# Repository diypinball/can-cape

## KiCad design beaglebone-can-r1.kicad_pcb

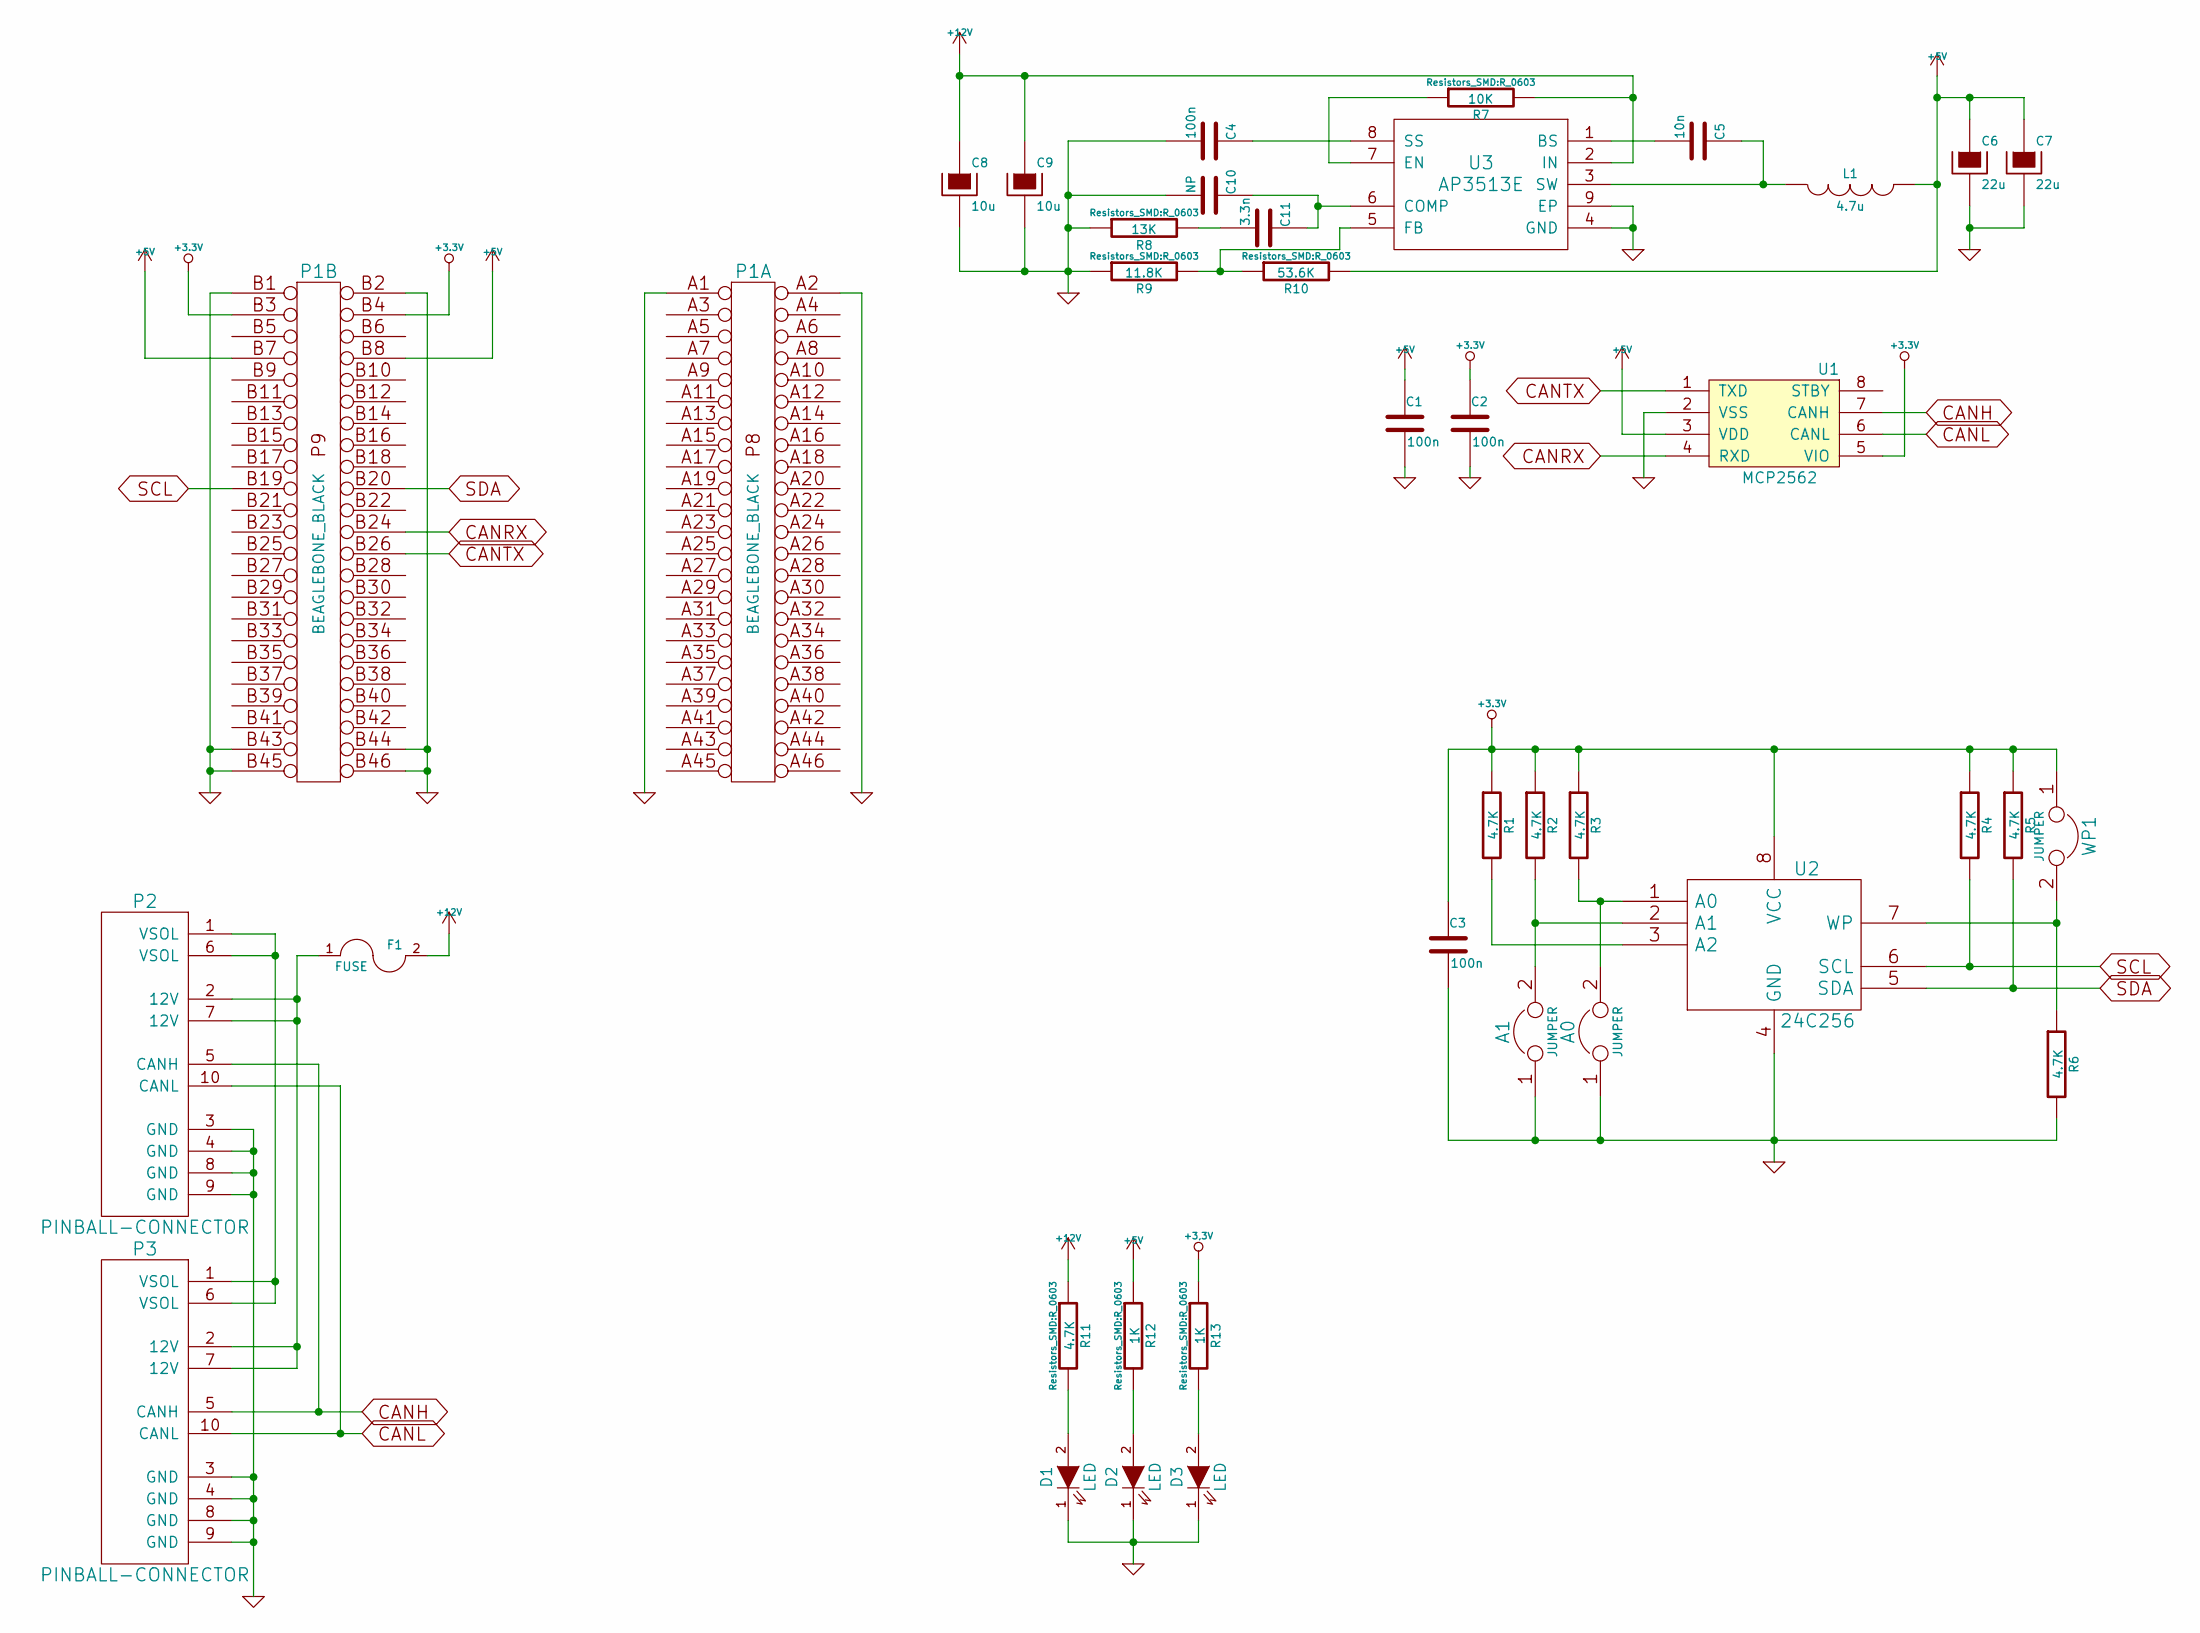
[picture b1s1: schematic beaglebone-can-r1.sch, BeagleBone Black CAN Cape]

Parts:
A0, A1: JUMPER; S_JUMPER_2
C1, C2, C3, C4: 100n; C_0603
C5: 10n; C_0603
C6, C7: 22u; c_elec_5x5.8
C8, C9: 10u; c_elec_5x5.8
C10: NP; C_0603
C11: 3.3n; C_0603
D1, D2, D3: LED; LED-0603
F1: FUSE; FC203-20MM
L1: 4.7u; SELF-WE-PD-XXL
P1: BEAGLEBONE_BLACK
P2, P3: PINBALL-CONNECTOR; PINBALL-CONNECTOR-V
R1, R2, R3, R4, R5, R6, R11: 4.7K; R_0603
R7: 10K; R_0603
R8: 13K; R_0603
R9: 11.8K; R_0603
R10: 53.6K; R_0603
R12, R13: 1K; R_0603
U1: MCP2562; SOIC-8_3.9x4.9mm_Pitch1.27mm
U2: 24C256; SOIC-8_3.9x4.9mm_Pitch1.27mm
U3: AP3513E; SOIC-8-1EP_3.9x4.9mm_Pitch1.27mm
WP1: JUMPER; S_JUMPER_2

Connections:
+5V: C1.1, C6.1, C7.1, L1.2, P1.B7 (P7), P1.B8 (P8), R10.2, R12.1, U1.3 (VDD)
+12V: C8.1, C9.1, F1.2, R7.2, R11.1, U3.2 (IN)
CANH: P2.5 (CANH), P3.5 (CANH), U1.7 (CANH)
CANL: P2.10 (CANL), P3.10 (CANL), U1.6 (CANL)
CANRX: P1.B24 (P24), U1.4 (RXD)
CANTX: P1.B26 (P26), U1.1 (TXD)
GND: A0.1, A1.1, C1.2, C2.2, C3.2, C4.2, C6.2, C7.2, C8.2, C9.2, C10.2, D1.1 (K), D2.1 (K), D3.1 (K), P1.A1 (GND), P1.A2 (P2), P1.B1 (GND), P1.B2 (P2), P1.B43 (P43), P1.B44 (P44), P1.B45 (P45), P1.B46 (P46), P2.3 (GND), P2.4 (GND), P2.8 (GND), P2.9 (GND), P3.3 (GND), P3.4 (GND), P3.8 (GND), P3.9 (GND), R6.2, R8.1, R9.1, U1.2 (VSS), U2.4 (GND), U3.4 (GND), U3.9 (EP)
unnamed: A0.2, R3.2, U2.1 (A0)
unnamed: A1.2, R2.2, U2.2 (A1)
unnamed: C4.1, U3.8 (SS)
unnamed: C5.1, L1.1, U3.3 (SW)
unnamed: C5.2, U3.1 (BS)
unnamed: C10.1, C11.1, U3.6 (COMP)
unnamed: C11.2, R8.2
unnamed: D1.2 (A), R11.2
unnamed: D2.2 (A), R12.2
unnamed: D3.2 (A), R13.2
unnamed: F1.1, P2.2 (12V), P2.7 (12V), P3.2 (12V), P3.7 (12V)
unnamed: P2.1 (VSOL), P2.6 (VSOL), P3.1 (VSOL), P3.6 (VSOL)
unnamed: R1.2, U2.3 (A2)
unnamed: R6.1, U2.7 (WP), WP1.2
unnamed: R7.1, U3.7 (EN)
unnamed: R9.2, R10.1, U3.5 (FB)
SCL: P1.B19 (P19), R4.2, U2.6 (SCL)
SDA: P1.B20 (P20), R5.2, U2.5 (SDA)

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
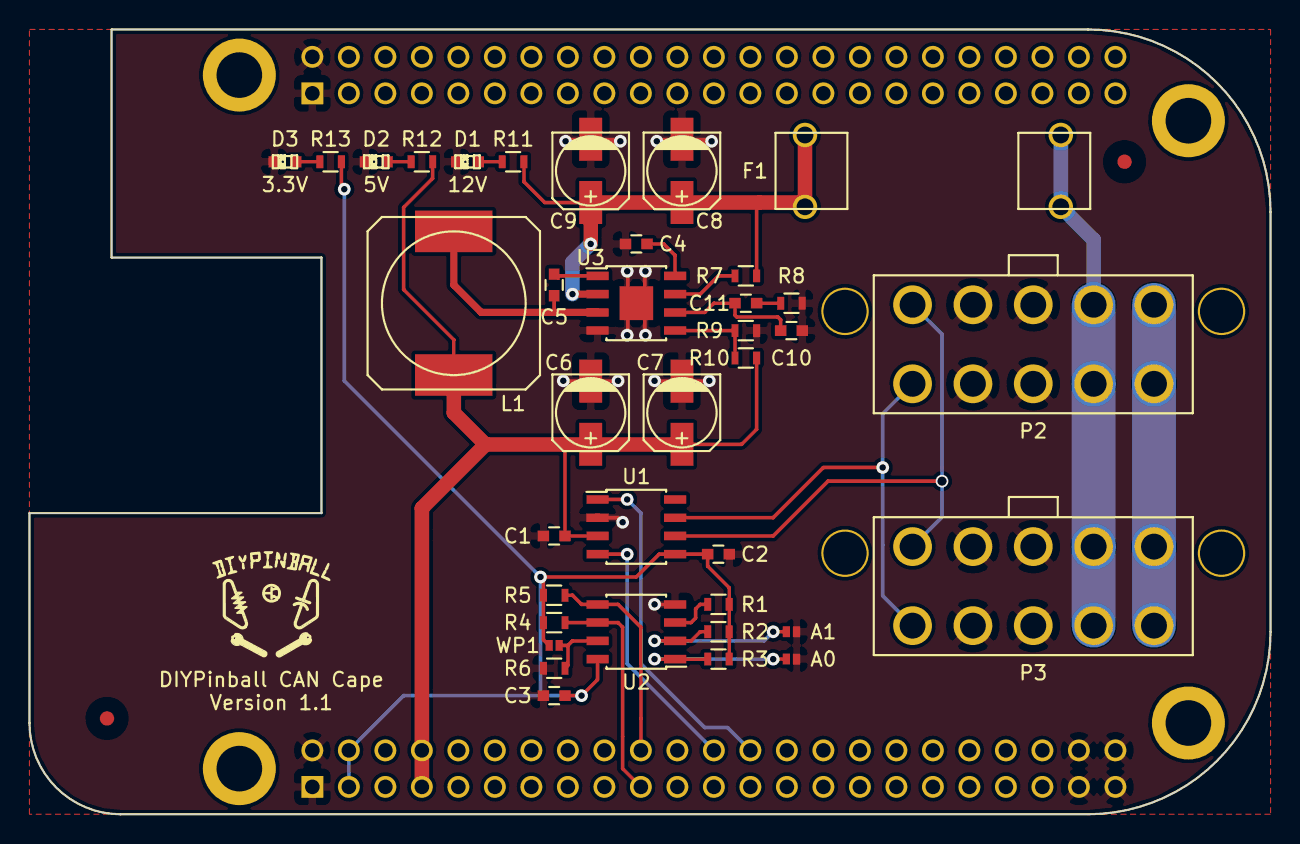
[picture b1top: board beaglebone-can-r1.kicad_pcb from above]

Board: 2 copper layers, 86.4 x 54.6 mm, 40 parts (0 on the bottom side), 26 nets.

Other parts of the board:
FIDUCIAL: VAL**; FIDUCIAL
FIDUCIAL#2: VAL**; FIDUCIAL

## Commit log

2015-06-07 Adding work done to datE
2016-09-09 A bunch of old updates
